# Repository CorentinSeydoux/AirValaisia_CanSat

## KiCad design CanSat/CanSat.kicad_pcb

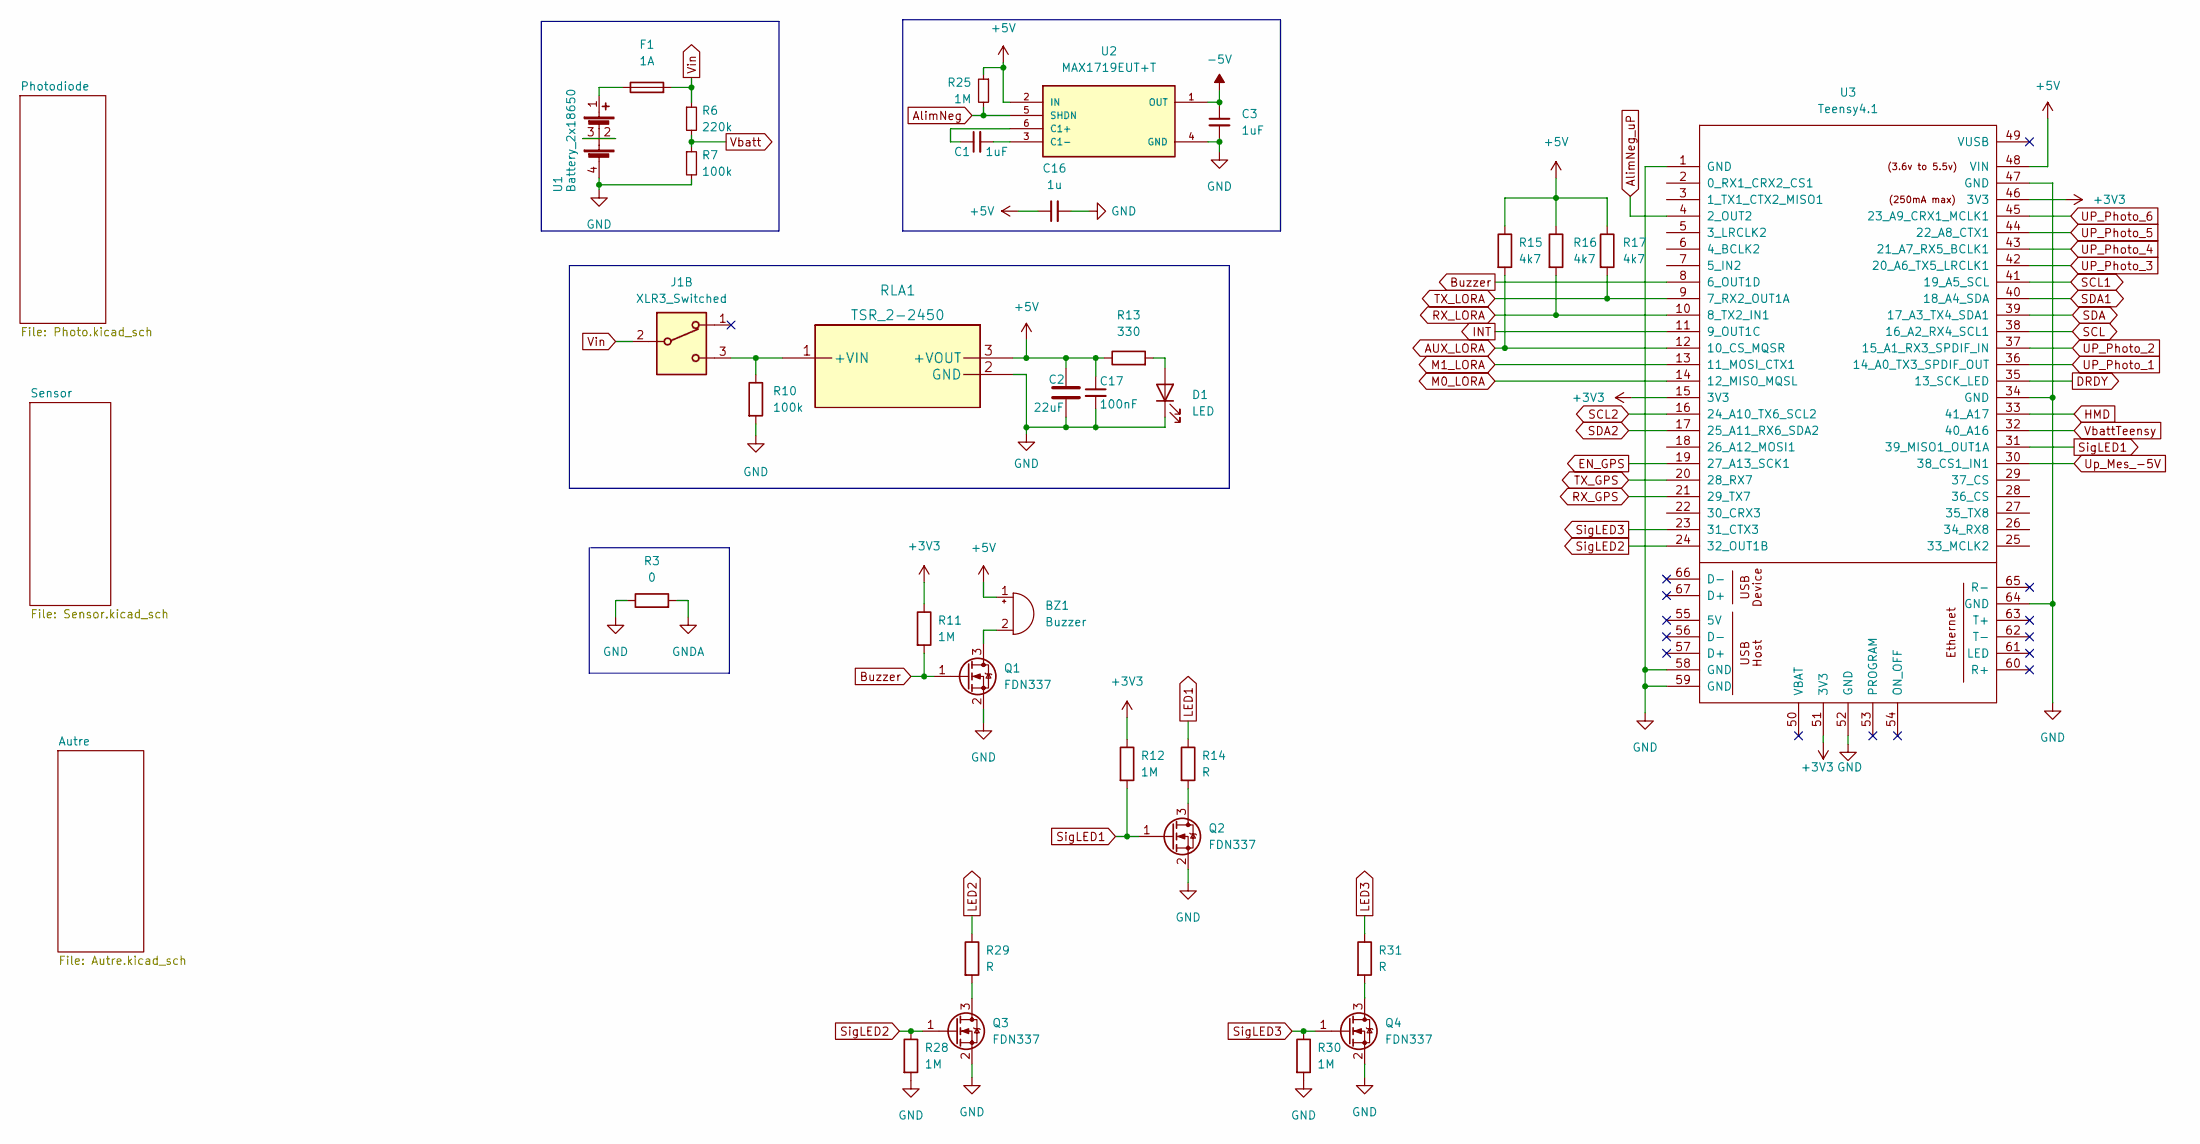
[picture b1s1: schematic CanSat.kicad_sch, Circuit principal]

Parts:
BZ1: Buzzer; KTG1205CL
C1, C3: 1uF; C_0805_2012Metric
C2: 22uF; CP_Elec_6.3x5.9
C16: 1u; C_0805_2012Metric_Pad1.18x1.45mm_HandSolder
C17: 100nF; C_0805_2012Metric_Pad1.18x1.45mm_HandSolder
D1: LED; D_0805_2012Metric_Pad1.15x1.40mm_HandSolder
F1: 1A; Fuseholder_Littelfuse_Nano2_154x
J1: XLR3_Switched; PinHeader_1x03_P2.54mm_Vertical
Q1, Q2, Q3, Q4: FDN337; SOT-23
R3: 0; R_0805_2012Metric_Pad1.20x1.40mm_HandSolder
R6: 220k; R_0805_2012Metric_Pad1.20x1.40mm_HandSolder
R7, R10: 100k; R_0805_2012Metric_Pad1.20x1.40mm_HandSolder
R11, R12, R25, R28, R30: 1M; R_0805_2012Metric_Pad1.20x1.40mm_HandSolder
R13: 330; R_0805_2012Metric_Pad1.20x1.40mm_HandSolder
R14, R29, R31: R; R_0805_2012Metric_Pad1.20x1.40mm_HandSolder
R15, R16, R17: 4k7; R_0805_2012Metric_Pad1.20x1.40mm_HandSolder
RLA1: TSR_2-2450; TSR 2-2450
U1: Battery_2x18650
U2: MAX1719EUT+T; SOT-23-6_Handsoldering
U3: Teensy4.1; Teensy41

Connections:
+3V3: R11.1, R12.1, U3.15 (3V3), U3.46 (3V3), U3.51 (3V3); also elsewhere on the board
+5V: BZ1.1 (-), C2.1, C16.1, C17.1, R13.1, R15.1, R16.1, R17.1, R25.1, RLA1.3 (+VOUT), U2.2 (IN), U3.48 (VIN); also elsewhere on the board
-5V: C3.1, U2.1 (OUT); also elsewhere on the board
AUX_LORA: R15.2, U3.12 (10_CS_MQSR); also elsewhere on the board
AlimNeg: R25.2, U2.5 (SHDN); also elsewhere on the board
AlimNeg_uP: U3.4 (2_OUT2); also elsewhere on the board
Buzzer: Q1.1 (G), R11.2, U3.8 (6_OUT1D)
DRDY: U3.35 (13_SCK_LED); also elsewhere on the board
EN_GPS: U3.19 (27_A13_SCK1); also elsewhere on the board
GND: C2.2, C3.2, C16.2, C17.2, D1.1 (K), Q1.2 (S), Q2.2 (S), Q3.2 (S), Q4.2 (S), R3.1, R7.2, R10.2, R28.2, R30.2, RLA1.2 (GND), U1.4, U2.4 (GND), U3.1 (GND), U3.34 (GND), U3.47 (GND), U3.52 (GND), U3.58 (GND), U3.59 (GND), U3.64 (GND); also elsewhere on the board
GNDA: R3.2; also elsewhere on the board
HMD: U3.33 (41_A17); also elsewhere on the board
INT: U3.11 (9_OUT1C); also elsewhere on the board
LED1: R14.1; also elsewhere on the board
LED2: R29.1; also elsewhere on the board
LED3: R31.1; also elsewhere on the board
M0_LORA: U3.14 (12_MISO_MQSL); also elsewhere on the board
M1_LORA: U3.13 (11_MOSI_CTX1); also elsewhere on the board
unnamed: BZ1.2 (+), Q1.3 (D)
unnamed: C1.1, U2.6 (C1+)
unnamed: C1.2, U2.3 (C1-)
unnamed: D1.2 (A), R13.2
unnamed: F1.1, U1.1
unnamed: J1.3, R10.1, RLA1.1 (+VIN)
unnamed: Q2.3 (D), R14.2
unnamed: Q3.3 (D), R29.2
unnamed: Q4.3 (D), R31.2
unnamed: U1.2, U1.3
RX_GPS: U3.21 (29_TX7); also elsewhere on the board
RX_LORA: R16.2, U3.10 (8_TX2_IN1); also elsewhere on the board
SCL: U3.38 (16_A2_RX4_SCL1); also elsewhere on the board
SCL1: U3.41 (19_A5_SCL); also elsewhere on the board
SCL2: U3.16 (24_A10_TX6_SCL2); also elsewhere on the board
SDA: U3.39 (17_A3_TX4_SDA1); also elsewhere on the board
SDA1: U3.40 (18_A4_SDA); also elsewhere on the board
SDA2: U3.17 (25_A11_RX6_SDA2); also elsewhere on the board
SigLED1: Q2.1 (G), R12.2, U3.31 (39_MISO1_OUT1A)
SigLED2: Q3.1 (G), R28.1, U3.24 (32_OUT1B)
SigLED3: Q4.1 (G), R30.1, U3.23 (31_CTX3)
TX_GPS: U3.20 (28_RX7); also elsewhere on the board
TX_LORA: R17.2, U3.9 (7_RX2_OUT1A); also elsewhere on the board
UP_Photo_1: U3.36 (14_A0_TX3_SPDIF_OUT); also elsewhere on the board
UP_Photo_2: U3.37 (15_A1_RX3_SPDIF_IN); also elsewhere on the board
UP_Photo_3: U3.42 (20_A6_TX5_LRCLK1); also elsewhere on the board
UP_Photo_4: U3.43 (21_A7_RX5_BCLK1); also elsewhere on the board
UP_Photo_5: U3.44 (22_A8_CTX1); also elsewhere on the board
UP_Photo_6: U3.45 (23_A9_CRX1_MCLK1); also elsewhere on the board
Up_Mes_-5V: U3.30 (38_CS1_IN1); also elsewhere on the board
Vbatt: R6.2, R7.1; also elsewhere on the board
VbattTeensy: U3.32 (40_A16); also elsewhere on the board
Vin: F1.2, J1.2, R6.1

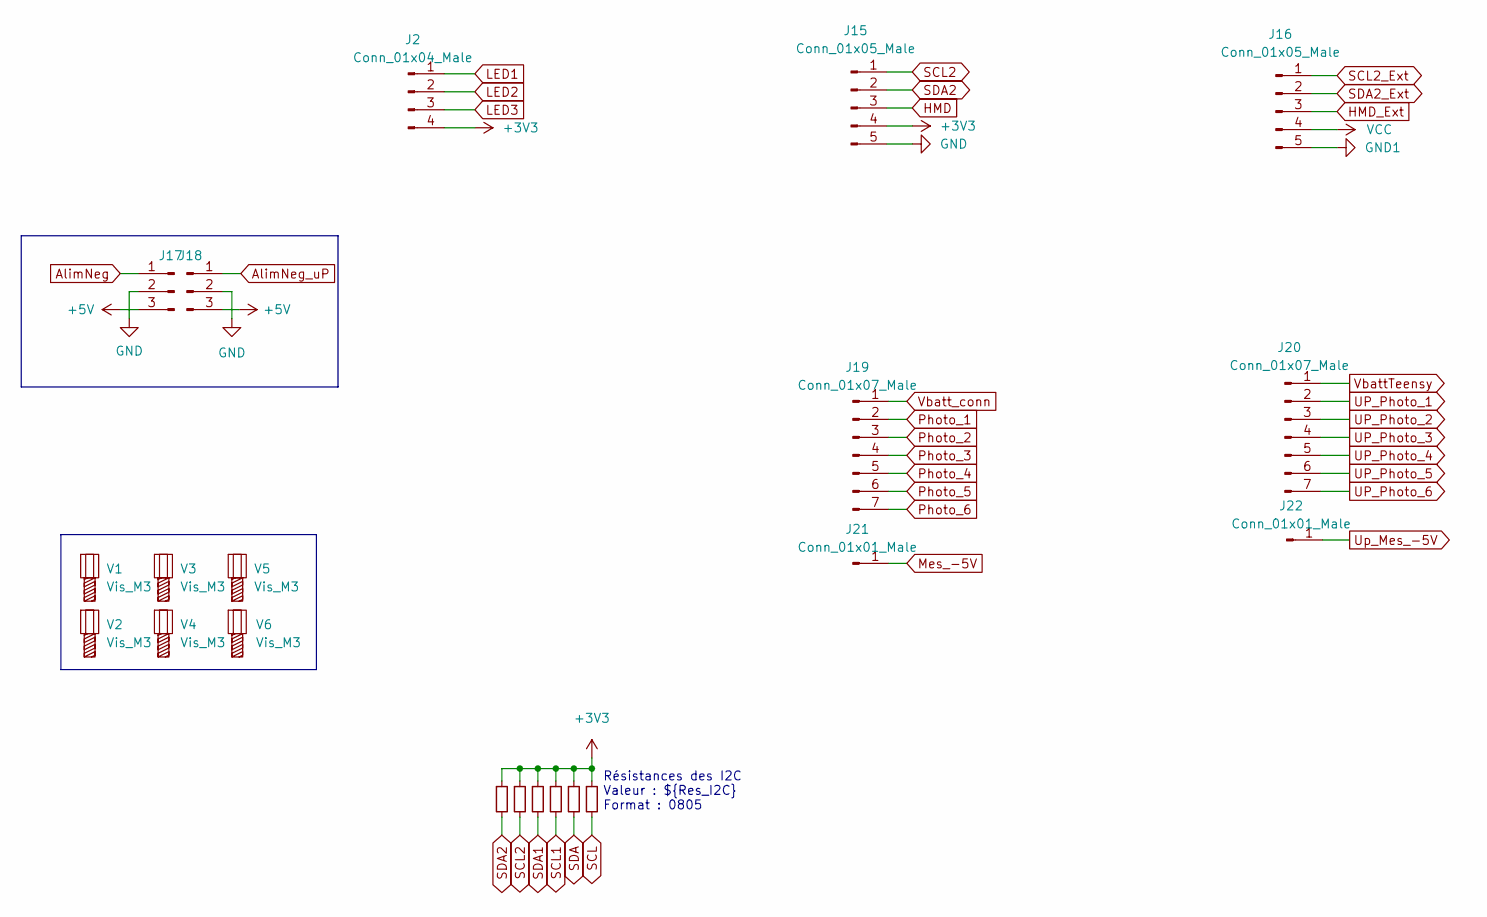
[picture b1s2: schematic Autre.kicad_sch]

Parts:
J2: Conn_01x04_Male; PinHeader_1x04_P2.54mm_Vertical
J15, J16: Conn_01x05_Male; PinHeader_1x05_P2.54mm_Vertical
J17, J18: Conn_01x03_Male; PinHeader_1x03_P2.54mm_Vertical
J19, J20: Conn_01x07_Male; PinHeader_1x07_P2.54mm_Vertical
J21, J22: Conn_01x01_Male; PinHeader_1x01_P2.54mm_Vertical
R1, R2, R4, R5, R8, R9: ${Res_I2C}; R_0805_2012Metric_Pad1.20x1.40mm_HandSolder
V1, V2, V3, V4, V5, V6: Vis_M3

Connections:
+3V3: J2.4, J15.4, R1.1, R2.1, R4.1, R5.1, R8.1, R9.1; also elsewhere on the board
+5V: J17.3, J18.3; also elsewhere on the board
AlimNeg: J17.1; also elsewhere on the board
AlimNeg_uP: J18.1; also elsewhere on the board
GND: J15.5, J17.2, J18.2; also elsewhere on the board
GND1: J16.5; also elsewhere on the board
HMD: J15.3; also elsewhere on the board
HMD_Ext: J16.3; also elsewhere on the board
LED1: J2.1; also elsewhere on the board
LED2: J2.2; also elsewhere on the board
LED3: J2.3; also elsewhere on the board
Mes_-5V: J21.1; also elsewhere on the board
Photo_1: J19.2; also elsewhere on the board
Photo_2: J19.3; also elsewhere on the board
Photo_3: J19.4; also elsewhere on the board
Photo_4: J19.5; also elsewhere on the board
Photo_5: J19.6; also elsewhere on the board
Photo_6: J19.7; also elsewhere on the board
SCL: R9.2; also elsewhere on the board
SCL1: R5.2; also elsewhere on the board
SCL2: J15.1, R2.2; also elsewhere on the board
SCL2_Ext: J16.1; also elsewhere on the board
SDA: R8.2; also elsewhere on the board
SDA1: R4.2; also elsewhere on the board
SDA2: J15.2, R1.2; also elsewhere on the board
SDA2_Ext: J16.2; also elsewhere on the board
UP_Photo_1: J20.2; also elsewhere on the board
UP_Photo_2: J20.3; also elsewhere on the board
UP_Photo_3: J20.4; also elsewhere on the board
UP_Photo_4: J20.5; also elsewhere on the board
UP_Photo_5: J20.6; also elsewhere on the board
UP_Photo_6: J20.7; also elsewhere on the board
Up_Mes_-5V: J22.1; also elsewhere on the board
VCC: J16.4; also elsewhere on the board
VbattTeensy: J20.1; also elsewhere on the board
Vbatt_conn: J19.1; also elsewhere on the board

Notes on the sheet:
Résistances des I2C Valeur : ${Res_I2C} Format : 0805

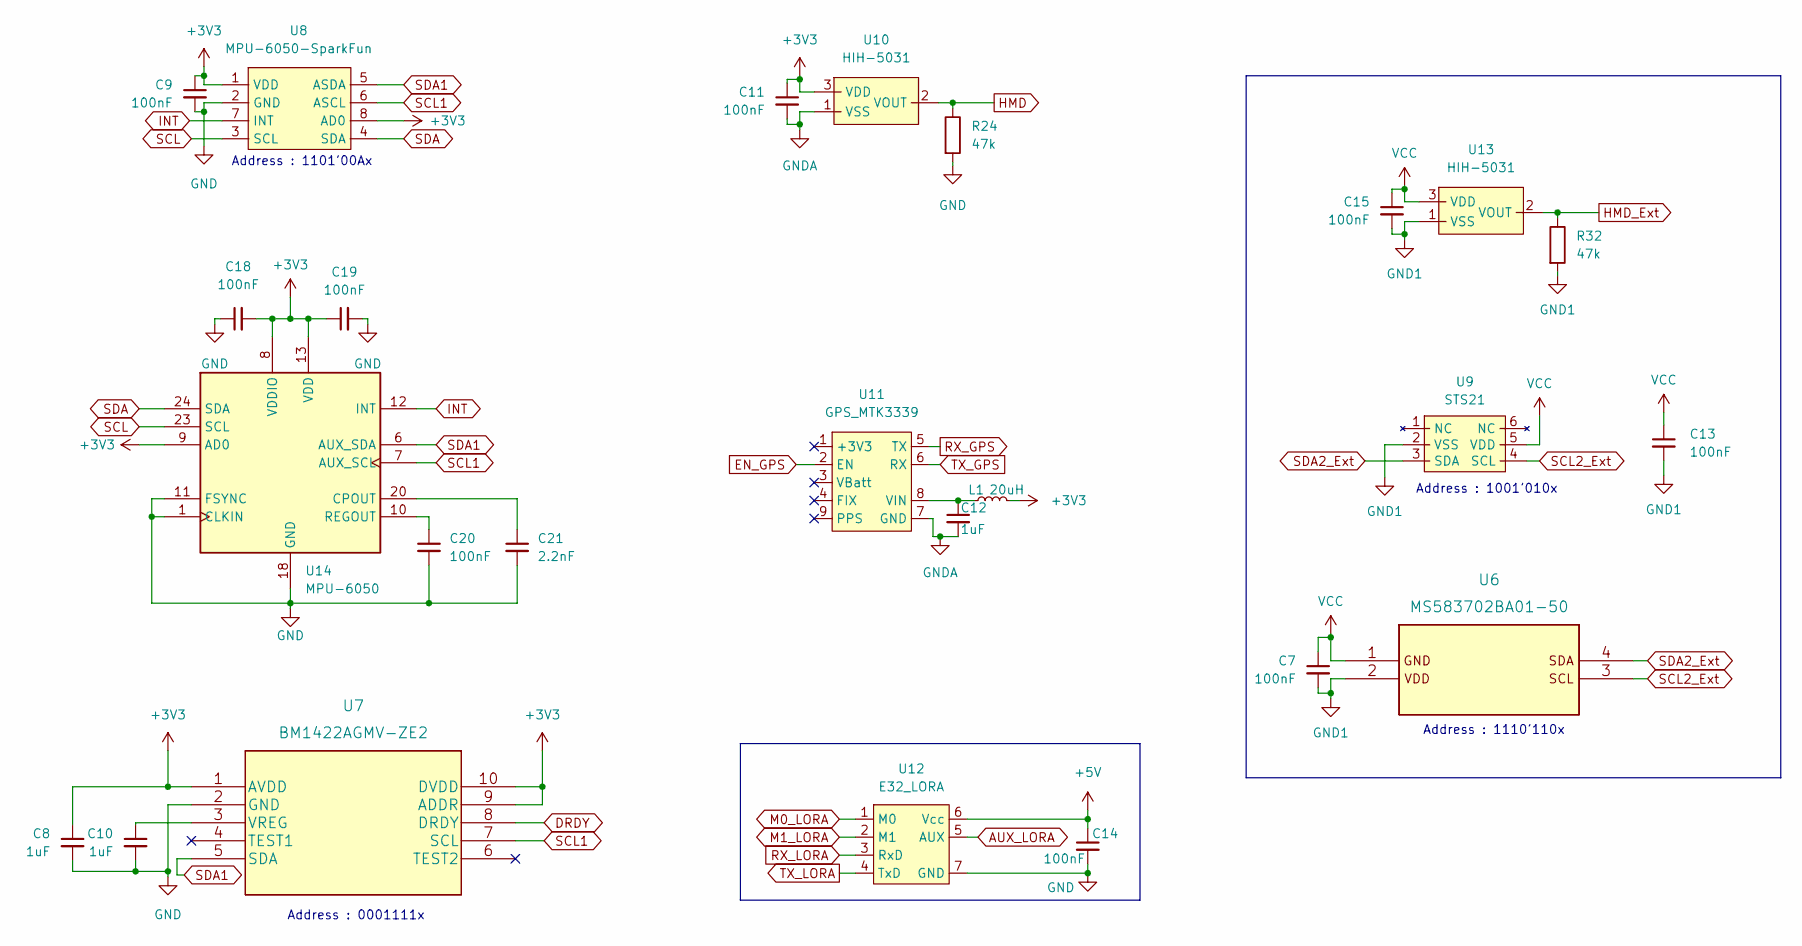
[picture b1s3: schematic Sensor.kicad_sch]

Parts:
C7, C9, C11, C13, C14, C15: 100nF; C_0805_2012Metric
C8, C10, C12: 1uF; C_0805_2012Metric
C18, C19, C20: 100nF; C_0805_2012Metric_Pad1.18x1.45mm_HandSolder
C21: 2.2nF; C_0805_2012Metric_Pad1.18x1.45mm_HandSolder
L1: 20uH; L_0805_2012Metric_Pad1.05x1.20mm_HandSolder
R24, R32: 47k; R_0805_2012Metric_Pad1.20x1.40mm_HandSolder
U6: MS583702BA01-50
U7: BM1422AGMV-ZE2
U8: MPU-6050-SparkFun; MPU6050
U9: STS21
U10, U13: HIH-5031; HIH-5031-001S
U11: GPS_MTK3339
U12: E32_LORA
U14: MPU-6050; InvenSense_QFN-24_4x4mm_P0.5mm

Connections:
+3V3: C8.1, C9.1, C11.1, C18.2, C19.1, L1.2, U7.1 (AVDD), U7.9 (ADDR), U7.10 (DVDD), U8.1 (VDD), U8.8 (AD0), U10.3 (VDD), U14.8 (VDDIO), U14.9 (AD0), U14.13 (VDD); also elsewhere on the board
+5V: C14.1, U12.6 (Vcc); also elsewhere on the board
AUX_LORA: U12.5 (AUX); also elsewhere on the board
DRDY: U7.8 (DRDY); also elsewhere on the board
EN_GPS: U11.2 (EN); also elsewhere on the board
GND: C8.2, C9.2, C10.2, C14.2, C18.1, C19.2, C20.2, C21.2, R24.2, U7.2 (GND), U8.2 (GND), U12.7 (GND), U14.1 (CLKIN), U14.11 (FSYNC), U14.18 (GND); also elsewhere on the board
GND1: C7.2, C13.2, C15.2, R32.2, U6.2 (VDD), U9.2 (VSS), U13.1 (VSS); also elsewhere on the board
GNDA: C11.2, C12.2, U10.1 (VSS), U11.7 (GND); also elsewhere on the board
HMD: R24.1, U10.2 (VOUT); also elsewhere on the board
HMD_Ext: R32.1, U13.2 (VOUT); also elsewhere on the board
INT: U8.7 (INT), U14.12 (INT); also elsewhere on the board
M0_LORA: U12.1 (M0); also elsewhere on the board
M1_LORA: U12.2 (M1); also elsewhere on the board
unnamed: C10.1, U7.3 (VREG)
unnamed: C12.1, L1.1, U11.8 (VIN)
unnamed: C20.1, U14.10 (REGOUT)
unnamed: C21.1, U14.20 (CPOUT)
RX_GPS: U11.5 (TX); also elsewhere on the board
RX_LORA: U12.3 (RxD); also elsewhere on the board
SCL: U8.3 (SCL), U14.23 (SCL); also elsewhere on the board
SCL1: U7.7 (SCL), U8.6 (ASCL), U14.7 (AUX_SCL); also elsewhere on the board
SCL2_Ext: U6.3 (SCL), U9.4 (SCL); also elsewhere on the board
SDA: U8.4 (SDA), U14.24 (SDA); also elsewhere on the board
SDA1: U7.5 (SDA), U8.5 (ASDA), U14.6 (AUX_SDA); also elsewhere on the board
SDA2_Ext: U6.4 (SDA), U9.3 (SDA); also elsewhere on the board
TX_GPS: U11.6 (RX); also elsewhere on the board
TX_LORA: U12.4 (TxD); also elsewhere on the board
VCC: C7.1, C13.1, C15.1, U6.1 (GND), U9.5 (VDD), U13.3 (VDD); also elsewhere on the board

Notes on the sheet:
Address : 0001111x
Address : 1101'00Ax
Address : 1001'010x
Address : 1110'110x

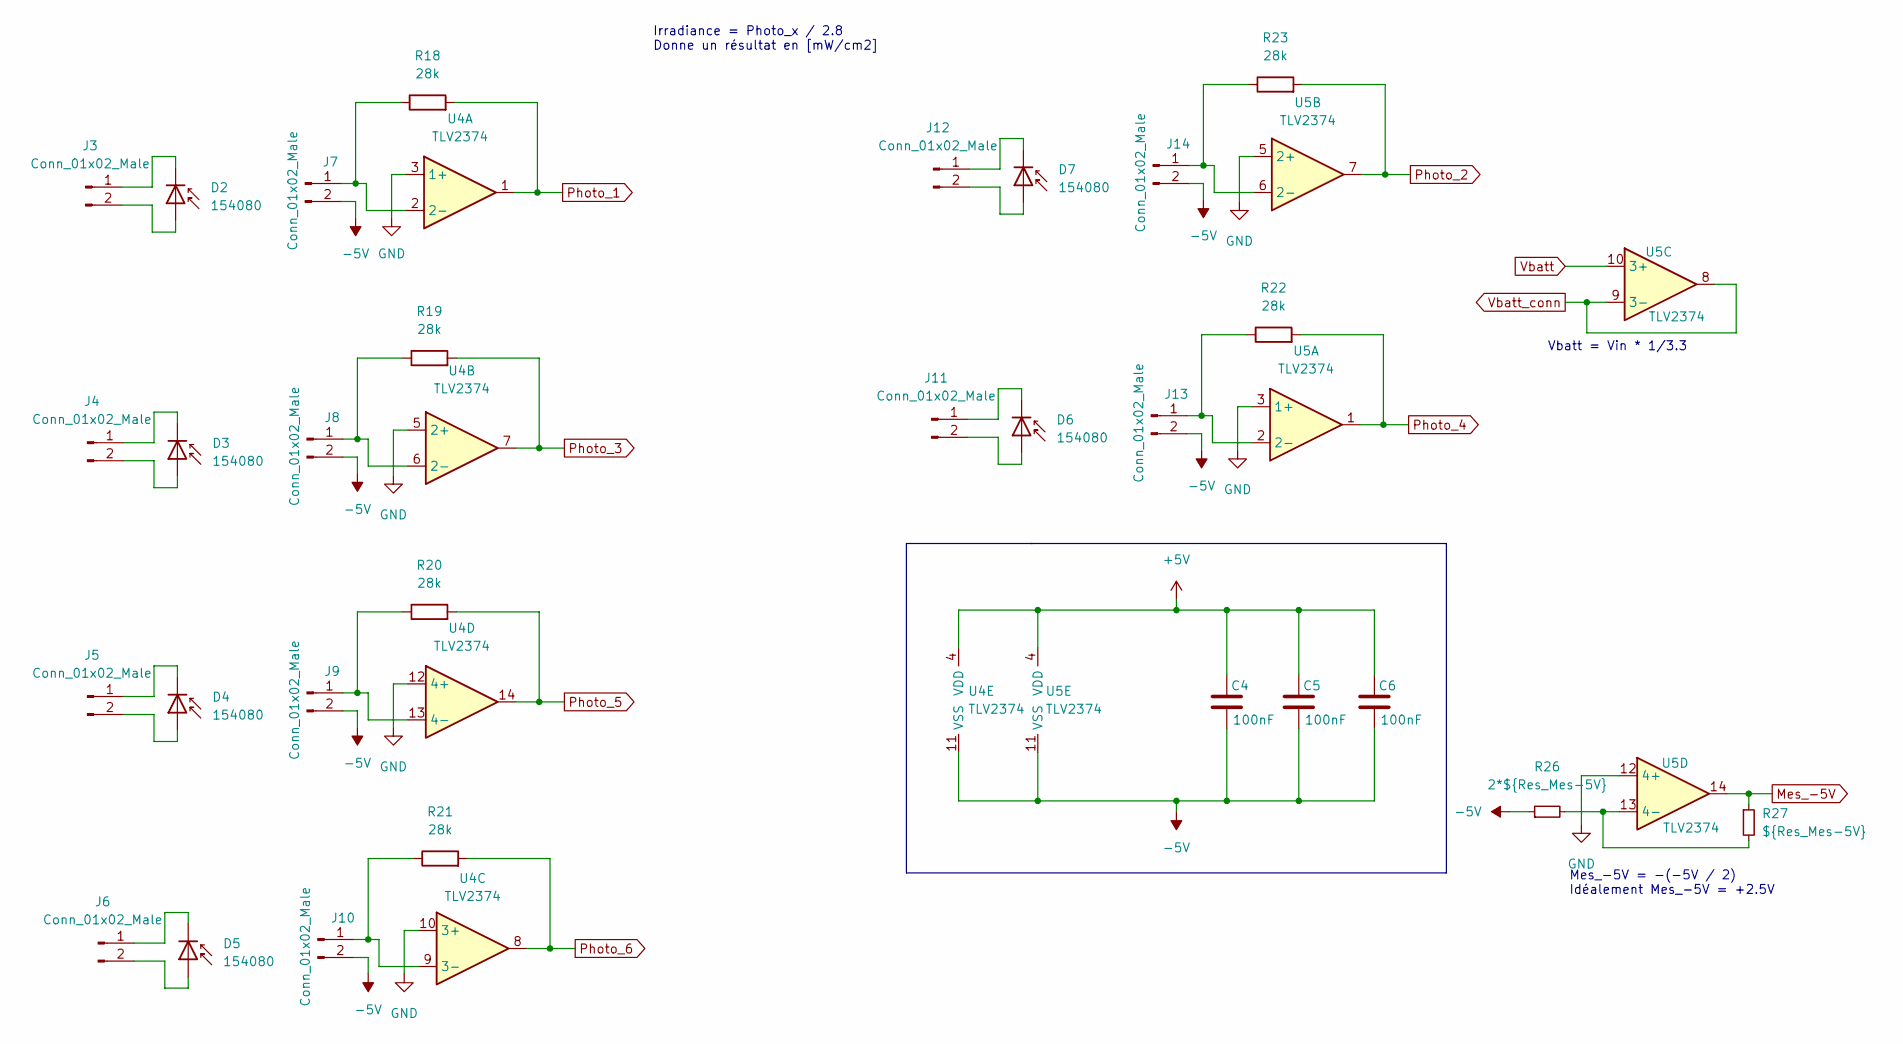
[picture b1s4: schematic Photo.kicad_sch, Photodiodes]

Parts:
C4, C5, C6: 100nF; C_0805_2012Metric
D2, D3, D4, D5, D6, D7: 154080; D_0805_2012Metric_Pad1.15x1.40mm_HandSolder
J3, J4, J5, J6, J7, J8, J9, J10, J11, J12, J13, J14: Conn_01x02_Male; PinHeader_1x02_P2.54mm_Vertical
R18, R19, R20, R21, R22, R23: 28k; R_0805_2012Metric_Pad1.20x1.40mm_HandSolder
R26: 2*${Res_Mes-5V}; R_0805_2012Metric_Pad1.20x1.40mm_HandSolder
R27: ${Res_Mes-5V}; R_0805_2012Metric_Pad1.20x1.40mm_HandSolder
U4, U5: TLV2374; SO-14_5.3x10.2mm_P1.27mm

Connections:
+5V: C4.1, C5.1, C6.1, U4.4 (VDD), U5.4 (VDD); also elsewhere on the board
-5V: C4.2, C5.2, C6.2, J7.2, J8.2, J9.2, J10.2, J13.2, J14.2, R26.1, U4.11 (VSS), U5.11 (VSS); also elsewhere on the board
GND: U4.3 (1+), U4.5 (2+), U4.10 (3+), U4.12 (4+), U5.3 (1+), U5.5 (2+), U5.12 (4+); also elsewhere on the board
Mes_-5V: R27.1, U5.14; also elsewhere on the board
unnamed: D2.1 (K), J3.1
unnamed: D2.2 (A), J3.2
unnamed: D3.1 (K), J4.1
unnamed: D3.2 (A), J4.2
unnamed: D4.1 (K), J5.1
unnamed: D4.2 (A), J5.2
unnamed: D5.1 (K), J6.1
unnamed: D5.2 (A), J6.2
unnamed: D6.1 (K), J11.1
unnamed: D6.2 (A), J11.2
unnamed: D7.1 (K), J12.1
unnamed: D7.2 (A), J12.2
unnamed: J7.1, R18.1, U4.2 (2-)
unnamed: J8.1, R19.1, U4.6 (2-)
unnamed: J9.1, R20.1, U4.13 (4-)
unnamed: J10.1, R21.1, U4.9 (3-)
unnamed: J13.1, R22.1, U5.2 (2-)
unnamed: J14.1, R23.1, U5.6 (2-)
unnamed: R26.2, R27.2, U5.13 (4-)
Photo_1: R18.2, U4.1; also elsewhere on the board
Photo_2: R23.2, U5.7; also elsewhere on the board
Photo_3: R19.2, U4.7; also elsewhere on the board
Photo_4: R22.2, U5.1; also elsewhere on the board
Photo_5: R20.2, U4.14; also elsewhere on the board
Photo_6: R21.2, U4.8; also elsewhere on the board
Vbatt: U5.10 (3+); also elsewhere on the board
Vbatt_conn: U5.8, U5.9 (3-); also elsewhere on the board

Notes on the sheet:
Vbatt = Vin * 1/3.3
Mes_-5V = -(-5V / 2) Idéalement Mes_-5V = +2.5V
Irradiance = Photo_x / 2.8 Donne un résultat en [mW/cm2]

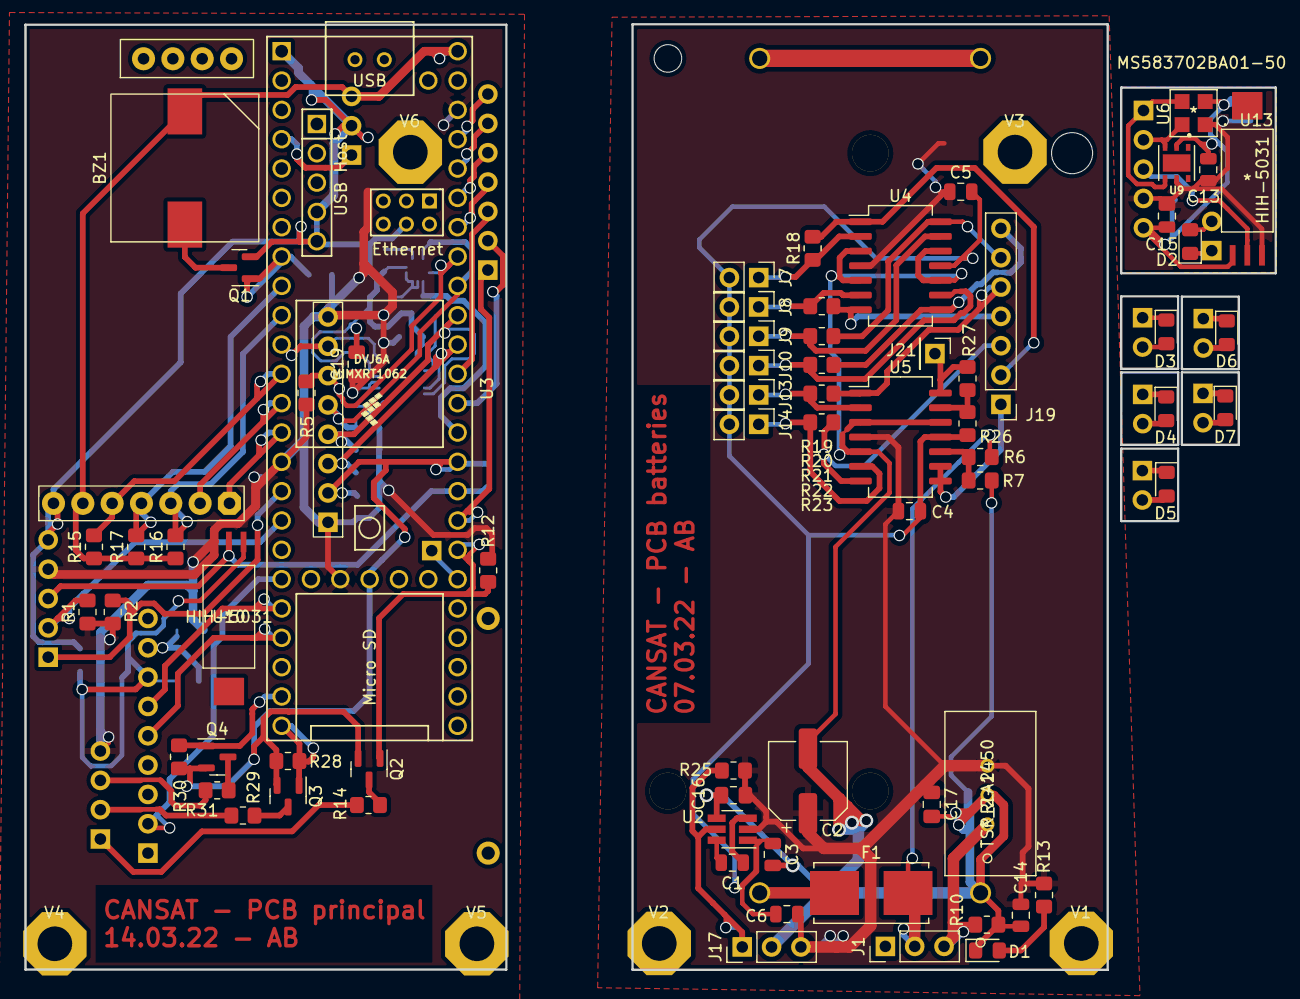
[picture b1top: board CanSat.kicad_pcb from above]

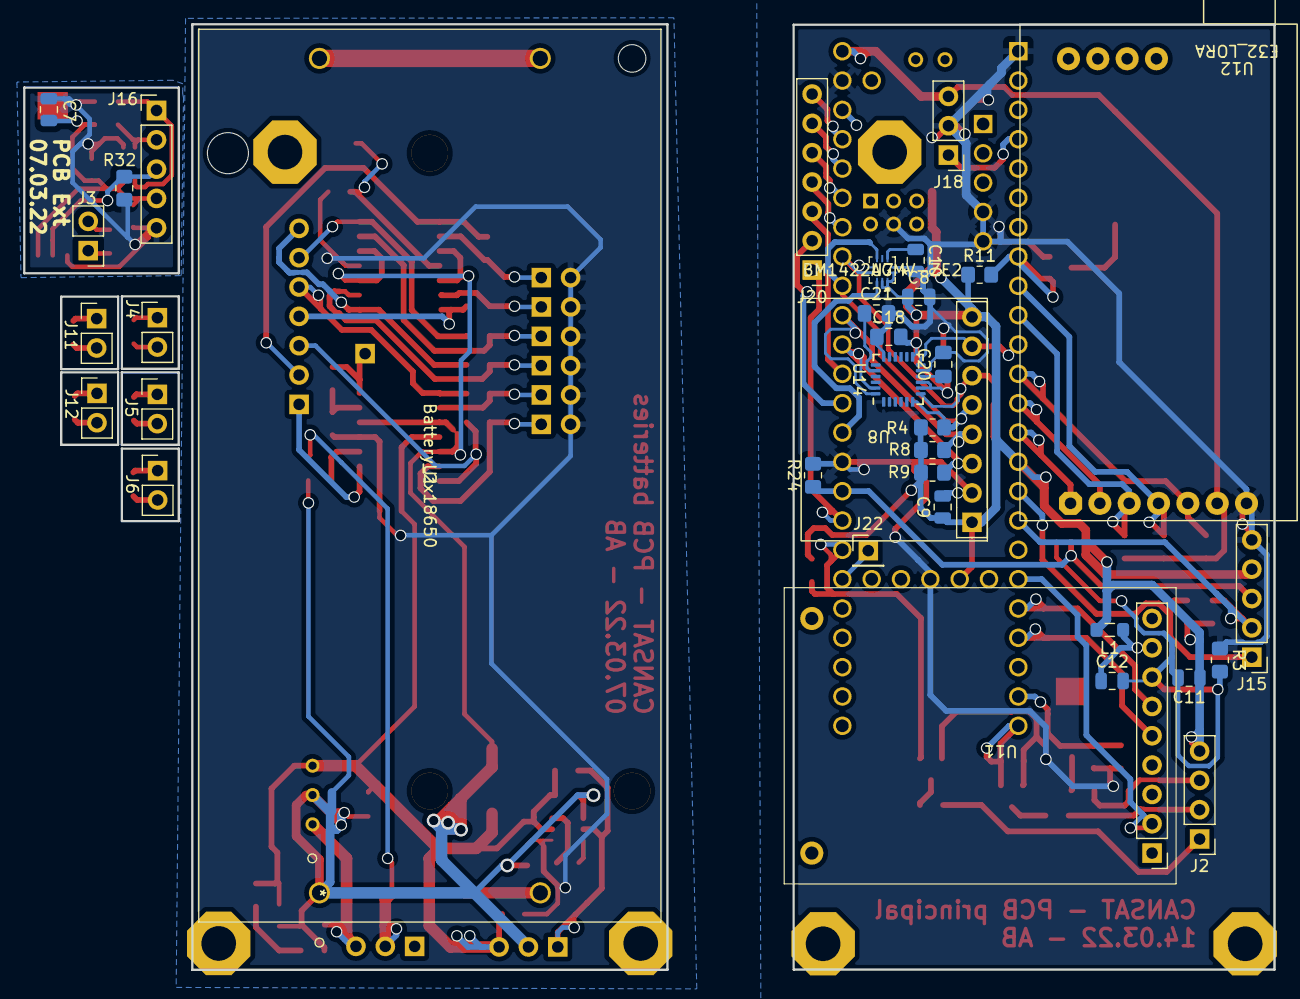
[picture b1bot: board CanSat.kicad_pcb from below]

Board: 2 copper layers, 108.3 x 81.9 mm, 110 parts (35 on the bottom side), 87 nets.

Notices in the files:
parts and their libraries:
Copyright 2021 Accelerated Designs. All rights reserved.
